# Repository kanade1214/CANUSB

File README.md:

# CANUSB 

created by kanade @kanade___1214

CAN通信とUSBのブリッジ基板です。  
高専ロボコン2023用に作成したものを配布用に安価に、誰でも使えるようにしました。  
作成、使用は自由ですが、kanadeに一声DMしていただけると喜びます。つながりを増やしたいので  

2024/1/28現在テスト期間につきプログラムの動作確認ができていない状況です。  
テスト期間が終わるまで少々お待ちください。  
代わりにPCでmidiを再生するとCANのパケットにするプログラムを入れてあります。

プログラムを書き込む前にプログラムの中にあるUSBのPIDをご自身のものに書き換えてください。  
~そのままで動く！わからない人はそのままで！~  

ROS2パッケージの説明を下に記述します。
(ROS2協力：@Pine_Pino_Pine)

# ROS2 can_communication

文責：Pine

## 前提

- ROS 2 Humble と Ubuntu 22.04 で動作確認済み
- Pythonライブラリpyserialを使用
    
    ```bash
    $ pip install pyserial
    ```
    
- カスタムメッセージ`CanMsg.msg`を使用
    
    ```cpp
    bool channel
    bool frametype
    uint32 id
    byte dlc
    byte[<=8] data
    ```
    
- kanade設計のCAN-USB基板を使用

## トピック

### publish

USB-CAN基板から受け取ったCANパケットをCanMsg型topic`/can_rx`としてpublishする

### subscribe

subscribeしたCanMsg型topic`/can_tx`をUSB-CAN基板にserialとして流す

## 通信仕様

### Serial

|  | 1 byte目 | 2 byte目 | 3 byte目 | 4~6 byte目 | 7 byte目 | 8~15 byte目 | 最後 |
| --- | --- | --- | --- | --- | --- | --- | --- |
| 目的 | メッセージ開始 | チャンネル | フレームタイプ | ID | DLC | データ | メッセージ終了 |
| 形式 | 0x02 | ASCIIコード | ASCIIコード | ASCIIコード | ASCIIコード |  | 0x03 |
| 備考 | tx時のみ　rxでは無し | ‘0’ or ‘1’ | ‘0’ or ‘1’ | 16進数 3桁 | ’1’ ~ ‘8’ | DLCに対応した長さ | tx時のみ　rxでは無し |

フレームタイプが1（リモートフレーム）のときはDLCに関わらずdataは無効（rx時は無視され、tx時は空）

### CanMsg

|  | 目的 | 型 (ROS) | 型 (Python) | 型 (C++) | 形式 |
| --- | --- | --- | --- | --- | --- |
| channel | 使用するCAN Busのチャンネル | bool | bool | bool | false: ch0　true: ch1 |
| frametype | データフレームとリモートフレームの選択 | bool | bool | bool | false: データフレーム　true: リモートフレーム |
| id | CANデバイスのID | uint32 | int | uint32_t | 非負整数（例：0x201なら513） |
| dlc | データのbyte長 | byte | bytes | uint8_t | ASCIIコード 1文字 |
| data | データ | byte配列 | bytesリスト | uint8_t配列 | 各デバイスの仕様による |

## Pythonでの使用例

### TX

```python
import rclpy
from rclpy.node import Node
from custom_messages.msg import CanMsg

class publisher(Node) :
    def __init__(self) :
        super().__init__('publisher')
        
        self.pub = self.create_publisher(CanMsg, '/can_tx', 1)
        
        # 1秒周期で整数値とテキストを送信させる
        self.create_timer(1, self.publish_integer)
        self.create_timer(1, self.publish_text)
    
    def publish_integer(self) :
        # 送信する数値（符号なし8bit整数型の範囲内）
        num = 120
        
        msg = CanMsg()
        msg.channel = False
        msg.frametype = False
        msg.id = 0x101
        msg.dlc = b'1'                  # int型でもstr型でもなくbytes型
        msg.data = [str(num).encode()]  # 要素が一つでもリストにする
        
        self.pub.publish(msg)
        
    def publish_text(self) :
        # 送信するテキスト（str型ではなくbytes型）
        txt = b'Hello'
        
        msg = CanMsg()
        msg.channel = False
        msg.frametype = False
        msg.id = 0x102
        msg.dlc = str(len(txt)).encode()      # DLCを自動設定
        msg.data = [bytes([c]) for c in txt]  # これが少し複雑なので注意
        
        self.pub.publish(msg)

def main() :
    rclpy.init()
    node = publisher()
    
    try :
        rclpy.spin(node)
    except Exception :
        node.destroy_node()
        rclpy.shutdown()

if __name__ == '__main__' :
    main()
```

### RX

```python
import rclpy
from rclpy.node import Node
from custom_messages.msg import CanMsg

class subscriber(Node) :
    def __init__(self) :
        super().__init__('subscriber')
        
        self.data1 = 0
        self.data2 = 0
        
        self.sub = self.create_subscription(CanMsg, '/can_rx', self.callback, 10)
    
    def callback(self, msg) :
　　　　　# idによって処理を分岐
        if msg.id == 0x201 :
            # 整数値が1byteで送信される場合
            self.data1 = int.from_bytes(msg.data[0], 'big')
        elif msg.id == 0x202 :
            # 整数値がASCIIコード列として送信される場合
            self.data2 = int(b''.join(msg.data))

def main() :
    rclpy.init()
    node = subscriber()
    
    try :
        rclpy.spin(node)
    except Exception :
        node.destroy_node()
        rclpy.shutdown()

if __name__ == '__main__' :
    main()
```

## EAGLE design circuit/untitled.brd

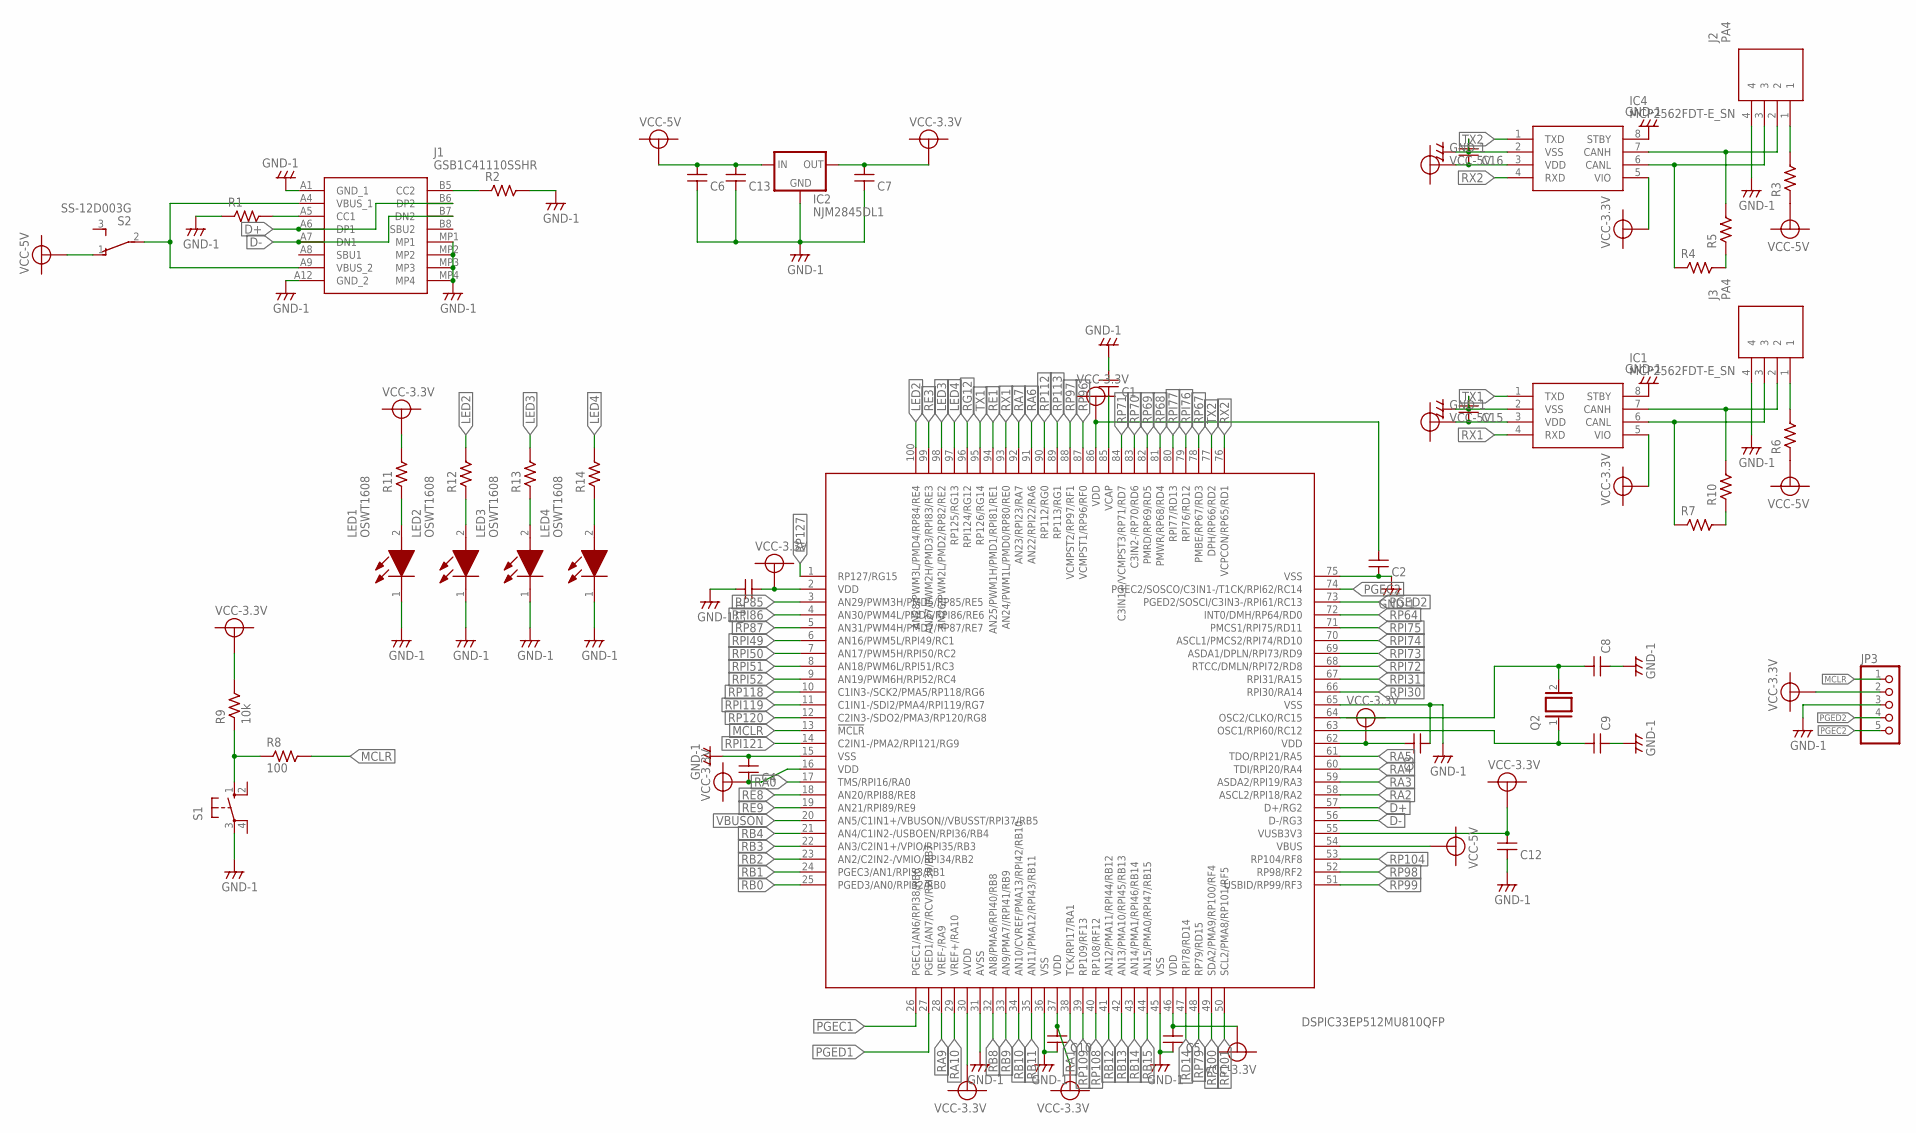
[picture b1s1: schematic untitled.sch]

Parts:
C1, C2, C3, C4, C5, C10, C11, C12, C13, C15, C16: CC1068; C1608
C6, C7: CC3216; C3216
C8, C9: CC2.54; C:1
IC1, IC4: MCP2562FDT-E_SN; SOIC127P600X175-8N
IC2: NJM2845DL1; TO252
IC3: DSPIC33EP512MU810QFP; TQFP100_0.5
J1: GSB1C41110SSHR
J2, J3: PA4
JP3: PINHD-1X5/90; 1X05/90
LED1, LED2, LED3, LED4: OSWT1608; LEDC1608X70N
Q2: XTAL/S; QS
R1, R2, R3, R4, R5, R6, R7, R10, R11, R12, R13, R14: R1/10W; C1608
R8: 100; C1608
R9: 10k; C1608
S1: 10-XX; B3F-10XX
S2: SS-12D003G

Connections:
+3.3V: C2.1, C3.2, C4.2, C5.1, C7.1, C10.1, C11.1, C12.1, IC1.5 (VIO), IC2.3 (OUT), IC3.2 (VDD), IC3.16 (VDD), IC3.30 (AVDD), IC3.37 (VDD), IC3.46 (VDD), IC3.55 (VUSB3V3), IC3.62 (VDD), IC3.86 (VDD), IC4.5 (VIO), JP3.2, R9.2, R11.2
+5V: C6.1, C13.1, C15.2, C16.2, IC1.3 (VDD), IC2.1 (IN), IC3.54 (VBUS), IC4.3 (VDD), R3.1, R6.1, S2.1 (O)
D+: IC3.57 (D+/RG2), J1.A6 (DP1), J1.B6 (DP2)
D-: IC3.56 (D-/RG3), J1.A7 (DN1), J1.B7 (DN2)
GND: C1.1, C2.2, C3.1, C4.1, C5.2, C6.2, C7.2, C8.P$2, C9.P$2, C10.2, C11.2, C12.2, C13.2, C15.1, C16.1, IC1.2 (VSS), IC1.8 (STBY), IC2.2 (GND), IC3.15 (VSS), IC3.31 (AVSS), IC3.36 (VSS), IC3.45 (VSS), IC3.65 (VSS), IC3.75 (VSS), IC4.2 (VSS), IC4.8 (STBY), J1.A1 (GND_1), J1.A12 (GND_2), J1.MP1, J1.MP2, J1.MP3, J1.MP4, J2.4, J3.4, JP3.3, LED1.1 (K), LED2.1 (K), LED3.1 (K), LED4.1 (K), R1.1, R2.2, S1.3
LED2: IC3.100 (AN28/PWM3L/PMD4/RP84/RE4), R12.2
LED3: IC3.98 (AN26/PWM2L/PMD2/RP82/RE2), R13.2
LED4: IC3.97 (RP125/RG13), R14.2
MCLR: IC3.13 (!MCLR), JP3.1, R8.2
unnamed: C9.P$1, IC3.63 (OSC1/RPI60/RC12), Q2.1
unnamed: C8.P$1, IC3.64 (OSC2/CLKO/RC15), Q2.2
unnamed: IC4.7 (CANH), J2.2, R5.2
unnamed: IC4.6 (CANL), J2.3, R4.1
unnamed: C1.2, IC3.85 (VCAP)
unnamed: J2.1, R3.2
unnamed: R4.2, R5.1
unnamed: J1.B5 (CC2), R2.1
unnamed: J1.A5 (CC1), R1.2
unnamed: R8.1, R9.1, S1.1 (S)
unnamed: J1.A4 (VBUS_1), J1.A9 (VBUS_2), S2.2
unnamed: IC1.7 (CANH), J3.2, R10.2
unnamed: IC1.6 (CANL), J3.3, R7.1
unnamed: J3.1, R6.2
unnamed: R7.2, R10.1
unnamed: LED1.2 (A), R11.1
unnamed: LED2.2 (A), R12.1
unnamed: LED3.2 (A), R13.1
unnamed: LED4.2 (A), R14.1
PGEC1: IC3.26 (PGEC1/AN6/RPI38/RB6)
PGEC2: IC3.74 (PGEC2/SOSCO/C3IN1-/T1CK/RPI62/RC14), JP3.5
PGED1: IC3.27 (PGED1/AN7/RCV/RPI39/RB7)
PGED2: IC3.73 (PGED2/SOSCI/C3IN3-/RPI61/RC13), JP3.4
RA0: IC3.17 (TMS/RPI16/RA0)
RA1: IC3.38 (TCK/RPI17/RA1)
RA2: IC3.58 (ASCL2/RPI18/RA2)
RA3: IC3.59 (ASDA2/RPI19/RA3)
RA4: IC3.60 (TDI/RPI20/RA4)
RA5: IC3.61 (TDO/RPI21/RA5)
RA6: IC3.91 (AN22/RPI22/RA6)
RA7: IC3.92 (AN23/RPI23/RA7)
RA9: IC3.28 (VREF-/RA9)
RA10: IC3.29 (VREF+/RA10)
RB0: IC3.25 (PGED3/AN0/RPI32/RB0)
RB1: IC3.24 (PGEC3/AN1/RPI33/RB1)
RB2: IC3.23 (AN2/C2IN2-/VMIO/RPI34/RB2)
RB3: IC3.22 (AN3/C2IN1+/VPIO/RPI35/RB3)
RB4: IC3.21 (AN4/C1IN2-/USBOEN/RPI36/RB4)
RB8: IC3.32 (AN8/PMA6/RPI40/RB8)
RB9: IC3.33 (AN9/PMA7//RPI41/RB9)
RB10: IC3.34 (AN10/CVREF/PMA13/RPI42/RB10)
RB11: IC3.35 (AN11/PMA12/RPI43/RB11)
RB12: IC3.41 (AN12/PMA11/RPI44/RB12)
RB13: IC3.42 (AN13/PMA10/RPI45/RB13)
RB14: IC3.43 (AN14/PMA1/RPI46/RB14)
RB15: IC3.44 (AN15/PMA0/RPI47/RB15)
RD14: IC3.47 (RPI78/RD14)
RE1: IC3.94 (AN25/PWM1H/PMD1/RPI81/RE1)
RE3: IC3.99 (AN27/PWM2H/PMD3/RPI83/RE3)
RE8: IC3.18 (AN20/RPI88/RE8)
RE9: IC3.19 (AN21/RPI89/RE9)
RG12: IC3.96 (RPI124/RG12)
RP64: IC3.72 (INT0/DMH/RP64/RD0)
RP67: IC3.78 (PMBE/RP67/RD3)
RP68: IC3.81 (PMWR/RP68/RD4)
RP69: IC3.82 (PMRD/RP69/RD5)
RP70: IC3.83 (C3IN2-/RP70/RD6)
RP71: IC3.84 (C3IN1+/VCMPST3/RP71/RD7)
RP79: IC3.48 (RP79/RD15)
RP85: IC3.3 (AN29/PWM3H/PMD5/RP85/RE5)
RP87: IC3.5 (AN31/PWM4H/PMD7/RP87/RE7)
RP96: IC3.87 (VCMPST1/RP96/RF0)
RP97: IC3.88 (VCMPST2/RP97/RF1)
RP98: IC3.52 (RP98/RF2)
RP99: IC3.51 (USBID/RP99/RF3)
RP100: IC3.49 (SDA2/PMA9/RP100/RF4)
RP101: IC3.50 (SCL2/PMA8/RP101/RF5)
RP104: IC3.53 (RP104/RF8)
RP108: IC3.40 (RP108/RF12)
RP109: IC3.39 (RP109/RF13)
RP112: IC3.90 (RP112/RG0)
RP113: IC3.89 (RP113/RG1)
RP118: IC3.10 (C1IN3-/SCK2/PMA5/RP118/RG6)
RP120: IC3.12 (C2IN3-/SDO2/PMA3/RP120/RG8)
RP127: IC3.1 (RP127/RG15)
RPI30: IC3.66 (RPI30/RA14)
RPI31: IC3.67 (RPI31/RA15)
RPI49: IC3.6 (AN16/PWM5L/RPI49/RC1)
RPI50: IC3.7 (AN17/PWM5H/RPI50/RC2)
RPI51: IC3.8 (AN18/PWM6L/RPI51/RC3)
RPI52: IC3.9 (AN19/PWM6H/RPI52/RC4)
RPI72: IC3.68 (RTCC/DMLN/RPI72/RD8)
RPI73: IC3.69 (ASDA1/DPLN/RPI73/RD9)
RPI74: IC3.70 (ASCL1/PMCS2/RPI74/RD10)
RPI75: IC3.71 (PMCS1/RPI75/RD11)
RPI76: IC3.79 (RPI76/RD12)
RPI77: IC3.80 (RPI77/RD13)
RPI86: IC3.4 (AN30/PWM4L/PMD6/RPI86/RE6)
RPI119: IC3.11 (C1IN1-/SDI2/PMA4/RPI119/RG7)
RPI121: IC3.14 (C2IN1-/PMA2/RPI121/RG9)
RX1: IC1.4 (RXD), IC3.93 (AN24/PWM1L/PMD0/RP80/RE0)
RX2: IC3.76 (VCPCON/RP65/RD1), IC4.4 (RXD)
TX1: IC1.1 (TXD), IC3.95 (RP126/RG14)
TX2: IC3.77 (DPH/RP66/RD2), IC4.1 (TXD)
VBUSON: IC3.20 (AN5/C1IN1+/VBUSON//VBUSST/RPI37/RB5)

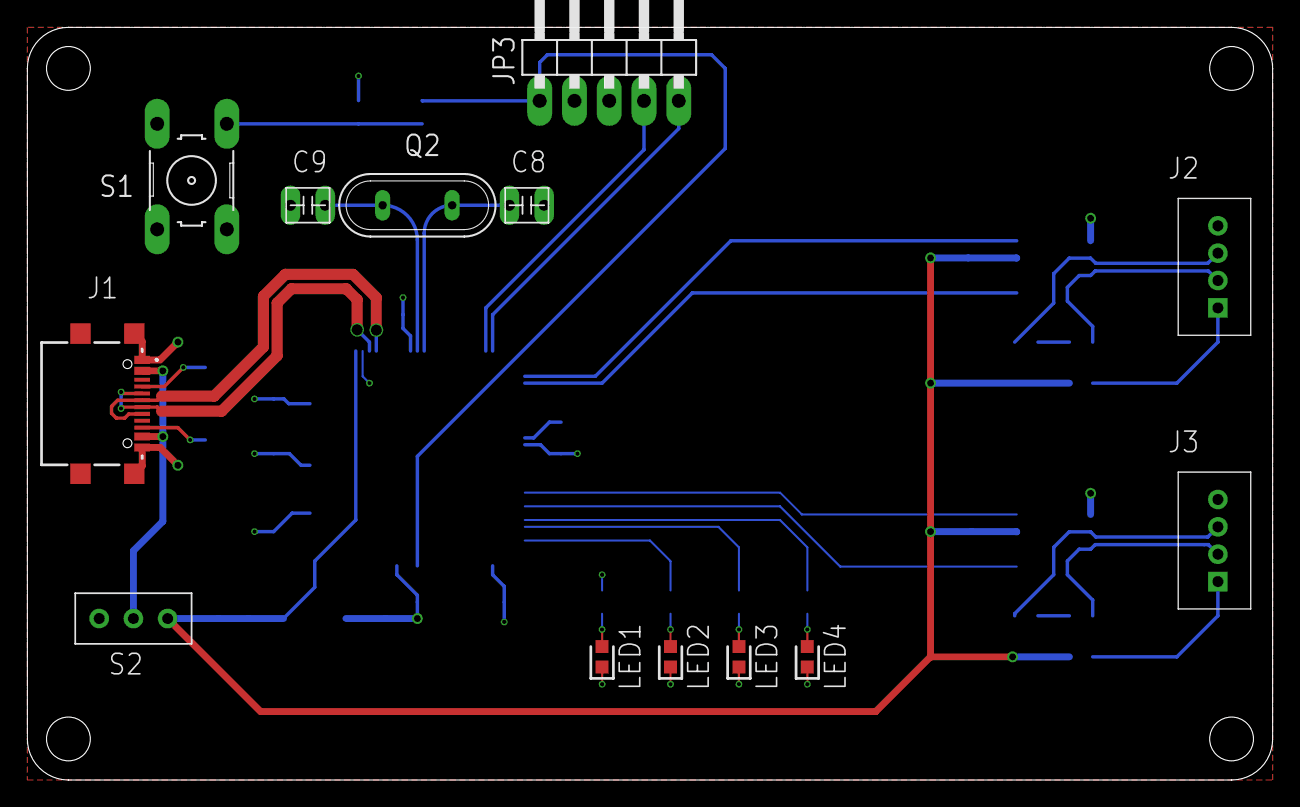
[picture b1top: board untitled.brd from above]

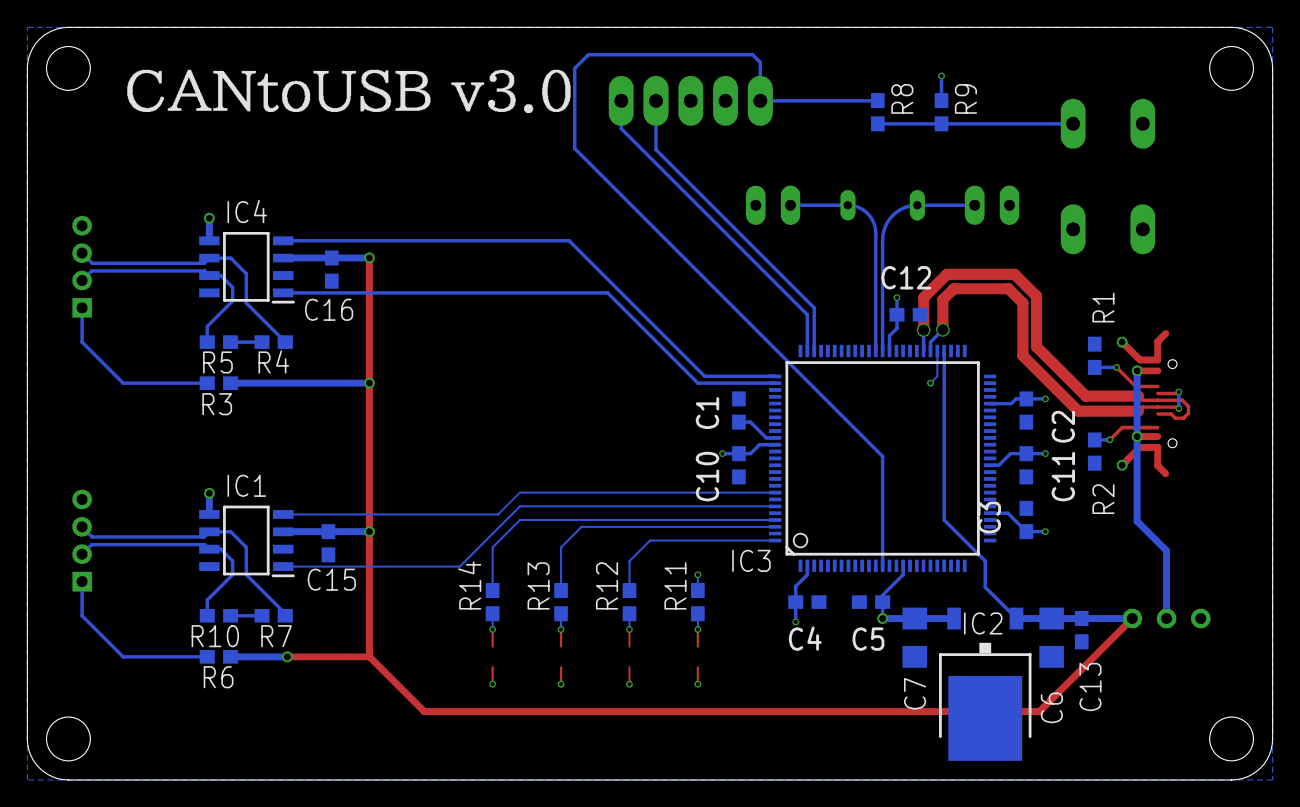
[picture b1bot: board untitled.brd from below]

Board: 2 copper layers, 91.0 x 55.0 mm, 44 parts (31 on the bottom side), 34 nets.

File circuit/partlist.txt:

Partlist

Exported from untitled.brd at 2024/01/12 18:44

EAGLE Version 9.6.2 Copyright (c) 1988-2020 Autodesk, Inc.

Assembly variant: 

Part     Value                Package            Library                    Position (mm)         Orientation

C1       10u                  C1608              Robocon-RLC                (39 27)               MR270
C2       0.1u                 C1608              Robocon-RLC                (18 27)               MR270
C3       0.1u                 C1608              Robocon-RLC                (18 19)               MR270
C4       0.1u                 C1608              Robocon-RLC                (34 13)               MR180
C5       0.1u                 C1608              Robocon-RLC                (29.35 13)            MR180
C6       100u                 C3216              Robocon-RLC                (16.15 10.4)          MR270
C7       100u                 C3216              Robocon-RLC                (26.15 10.4)          MR270
C8       0.1u                 C:1                Robocon-RLC                (36.5 42)             R0
C9       0.1u                 C:1                Robocon-RLC                (20.5 42)             R180
C10      0.1u                 C1608              Robocon-RLC                (39 23)               MR270
C11      0.1u                 C1608              Robocon-RLC                (18 23)               MR270
C12      0.1u                 C1608              Robocon-RLC                (26.6 34)             MR0
C13      0.1u                 C1608              Robocon-RLC                (13.95 10.95)         MR270
C15      0.1u                 C1608              Robocon-RLC                (69 17.3)             MR90
C16      0.1u                 C1608              Robocon-RLC                (68.75 37.3)          MR90
IC1      MCP2562FDT-E_SN      SOIC127P600X175-8N MCP2562FDT-E_SN            (75 17.5)             MR180
IC2      NJM2845DL1           TO252              Robocon-Regulator          (21 7)                MR180
IC3      DSPIC33EP512MU810QFP TQFP100_0.5        Robocon-PICMicroController (28.5 23.5)           MR90
IC4      MCP2562FDT-E_SN      SOIC127P600X175-8N MCP2562FDT-E_SN            (75 37.5)             MR180
J1       GSB1C41110SSHR       GSB1C41110SSHR     GSB1C41110SSHR             (5 27.5)              R270
J2       PA4                  PA4                Robocon-Connector          (87 34.5)             R270
J3       PA4                  PA4                Robocon-Connector          (87 14.5)             R270
JP3                           1X05/90            Robocon-Pin_Header         (42.52 53.44)         R0
LED1     OSWT1608             LEDC1608X70N       OSWT1608                   (42 9)                R90
LED2     OSWT1608             LEDC1608X70N       OSWT1608                   (47 9)                R90
LED3     OSWT1608             LEDC1608X70N       OSWT1608                   (52 9)                R90
LED4     OSWT1608             LEDC1608X70N       OSWT1608                   (57 9)                R90
Q2       12M                  QS                 Robocon-Other              (28.5 42)             R0
R1       5.1k                 C1608              Robocon-RLC                (13 31)               MR270
R2       5.1k                 C1608              Robocon-RLC                (13 24)               MR270
R3       0                    C1608              Robocon-RLC                (77 29)               MR180
R4       120                  C1608              Robocon-RLC                (73 32)               MR180
R5       0                    C1608              Robocon-RLC                (77 32)               MR180
R6       0                    C1608              Robocon-RLC                (77 9)                MR180
R7       120                  C1608              Robocon-RLC                (73 12)               MR180
R8       100                  C1608              Robocon-RLC                (28.85 48.8)          MR90
R9       10k                  C1608              Robocon-RLC                (24.2 48.8)           MR90
R10      0                    C1608              Robocon-RLC                (77 12)               MR180
R11      300                  C1608              Robocon-RLC                (42 13)               MR90
R12      300                  C1608              Robocon-RLC                (47 13)               MR90
R13      300                  C1608              Robocon-RLC                (52 13)               MR90
R14      300                  C1608              Robocon-RLC                (57 13)               MR90
S1                            B3F-10XX           Robocon-Switches           (12 45.4)             R270
S2       SS-12D003G           SS-12D003G         Robocon-Switches           (7.75 11.8)           R180

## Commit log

2024-01-12 add partlist
